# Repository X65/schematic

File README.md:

# X65

Modern 8-bit microcomputer

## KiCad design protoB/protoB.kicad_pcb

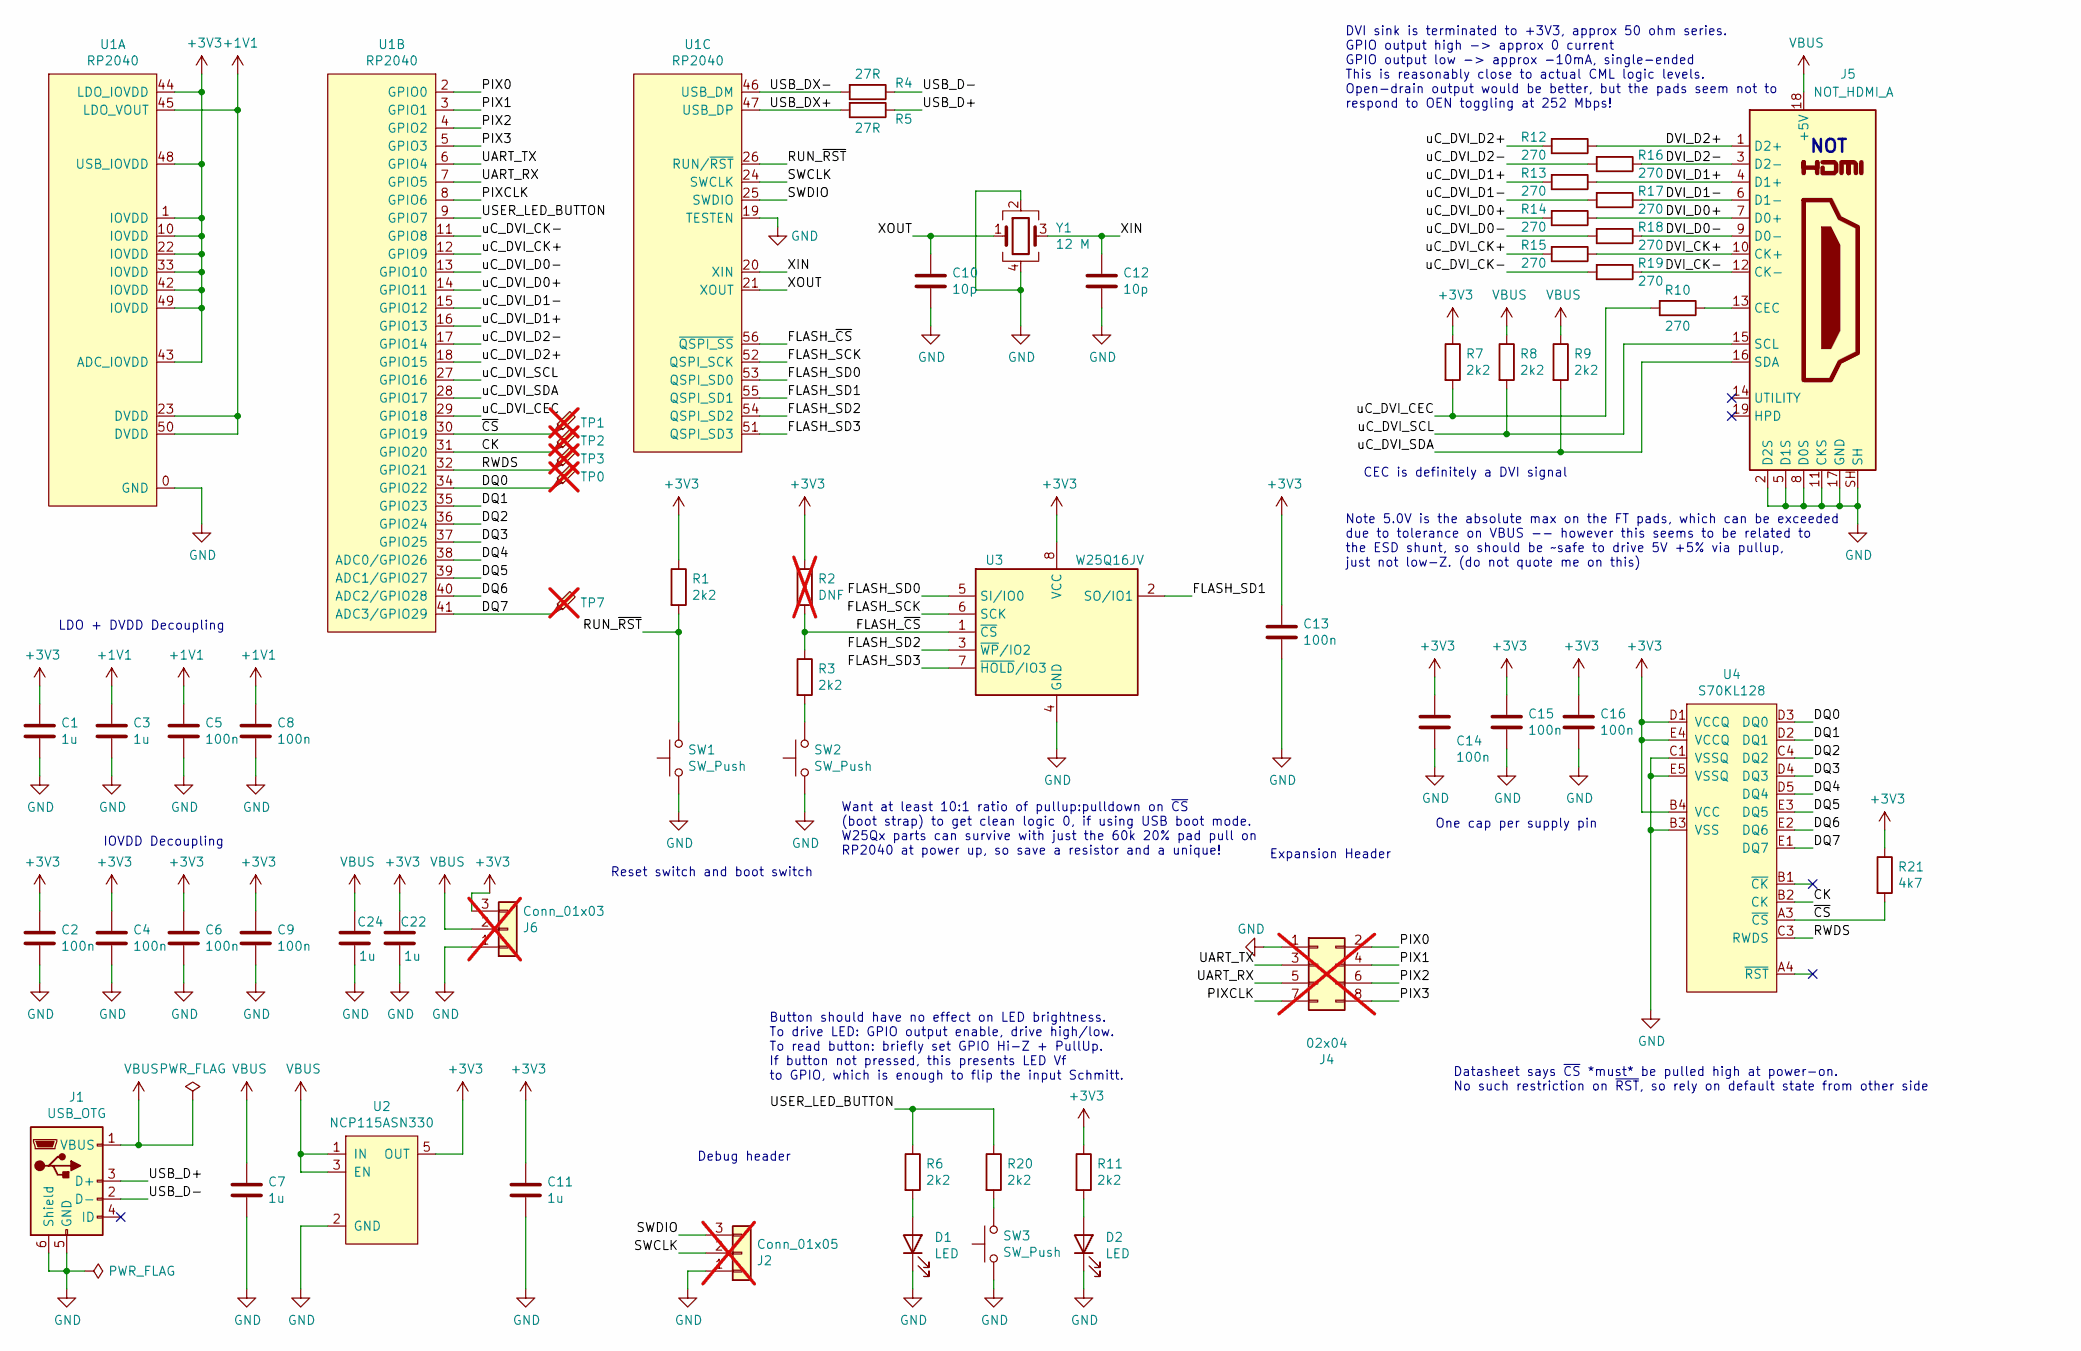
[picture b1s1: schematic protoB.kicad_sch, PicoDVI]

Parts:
C1, C3, C7, C11, C22, C24: 1u; C_0402_1005Metric; Manuf. PN CL05A105KP5NNNC
C2, C4, C5, C6, C8, C9, C13, C14, C15, C16: 100n; C_0402_1005Metric; Manuf. PN CL05A104KP5NNND
C10, C12: 10p; C_0402_1005Metric; Manuf. PN CL05C100JB5NNWC
D1, D2: LED; LED_0805_2012Metric; Manuf. PN LG R971-KN-1
J1: USB_OTG; USB_Micro-B_Molex-105017-0001; Manuf. PN 10118194-0001LF
J2: Conn_01x05; PinHeader_1x03_P2.54mm_Vertical; not fitted
J4: 02x04; PinHeader_2x04_P2.54mm_Vertical; not fitted
J5: NOT_HDMI_A; HDMI-SS-53000; Manuf. PN SS-53000-001
J6: Conn_01x03; PinHeader_1x03_P2.54mm_Vertical; not fitted
R1, R3, R6, R7, R8, R9, R11, R20: 2k2; R_0402_1005Metric; Manuf. PN ERJ-2GEJ222X
R2: DNF; R_0402_1005Metric; not fitted
R4, R5: 27R; R_0402_1005Metric; Manuf. PN ERJ-2GEJ270X
R10, R12, R13, R14, R15, R16, R17, R18, R19: 270; R_0402_1005Metric; Manuf. PN ERJ-2GEJ271X
R21: 4k7; R_0402_1005Metric; Manuf. PN ERJ-2GEJ472X
SW1, SW2, SW3: SW_Push; SW_SPST_PTS815; Manuf. PN TS20-42-25-WT-160-SMT-TR
TP0, TP1, TP2, TP3, TP7: TestPoint_Probe; TestPoint_Pad_1.0x1.0mm; not fitted
U1: RP2040; QFN-56_EP_7x7_Pitch0.4mm; Manuf. PN SC0914(13)
U2: NCP115ASN330; SOT-23-5_HandSoldering; Manuf. PN NCP115ASN330T2G
U3: W25Q16JV; WSON-8-1EP_6x5mm_P1.27mm_EP3.4x4mm; Manuf. PN W25Q16JVZPIM
U4: S70KL128; S70KS128; Manuf. PN S70KL1282GABHV020
Y1: 12 M; Crystal_SMD_3225-4Pin_3.2x2.5mm; Manuf. PN ABM8G-12.000MHZ-8-B2X-T

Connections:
+1V1: C3.1, C5.1, C8.1, U1.23 (DVDD), U1.45 (LDO_VOUT), U1.50 (DVDD)
+3V3: C1.1, C2.1, C4.1, C6.1, C9.1, C11.1, C13.1, C14.1, C15.1, C16.1, C22.1, J6.3, R1.1, R2.1, R7.1, R11.1, R21.1, U1.1 (IOVDD), U1.10 (IOVDD), U1.22 (IOVDD), U1.33 (IOVDD), U1.42 (IOVDD), U1.43 (ADC_IOVDD), U1.44 (LDO_IOVDD), U1.48 (USB_IOVDD), U1.49 (IOVDD), U2.5 (OUT), U3.8 (VCC), U4.B4 (VCC), U4.D1 (VCCQ), U4.E4 (VCCQ)
/CK: TP2.1, U1.31 (GPIO20), U4.B2 (CK)
/DQ0: TP0.1, U1.34 (GPIO22), U4.D3 (DQ0)
/DQ1: U1.35 (GPIO23), U4.D2 (DQ1)
/DQ2: U1.36 (GPIO24), U4.C4 (DQ2)
/DQ3: U1.37 (GPIO25), U4.D4 (DQ3)
/DQ4: U1.38 (ADC0/GPIO26), U4.D5 (DQ4)
/DQ5: U1.39 (ADC1/GPIO27), U4.E3 (DQ5)
/DQ6: U1.40 (ADC2/GPIO28), U4.E2 (DQ6)
/DQ7: TP7.1, U1.41 (ADC3/GPIO29), U4.E1 (DQ7)
/DVI_CK+: J5.10 (CK+), R15.1
/DVI_CK-: J5.12 (CK-), R19.1
/DVI_D0+: J5.7 (D0+), R14.1
/DVI_D0-: J5.9 (D0-), R18.1
/DVI_D1+: J5.4 (D1+), R13.1
/DVI_D1-: J5.6 (D1-), R17.1
/DVI_D2+: J5.1 (D2+), R12.1
/DVI_D2-: J5.3 (D2-), R16.1
/FLASH_SCK: U1.52 (QSPI_SCK), U3.6 (SCK)
/FLASH_SD0: U1.53 (QSPI_SD0), U3.5 (SI/IO0)
/FLASH_SD1: U1.55 (QSPI_SD1), U3.2 (SO/IO1)
/FLASH_SD2: U1.54 (QSPI_SD2), U3.3 (~WP/IO2)
/FLASH_SD3: U1.51 (QSPI_SD3), U3.7 (~HOLD/IO3)
/FLASH_~CS: R2.2, R3.1, U1.56 (~QSPI_SS), U3.1 (~CS)
/PIX0: J4.2, U1.2 (GPIO0)
/PIX1: J4.4, U1.3 (GPIO1)
/PIX2: J4.6, U1.4 (GPIO2)
/PIX3: J4.8, U1.5 (GPIO3)
/PIXCLK: J4.7, U1.8 (GPIO6)
/RUN_~RST: R1.2, SW1.2, U1.26 (RUN/~RST)
/RWDS: TP3.1, U1.32 (GPIO21), U4.C3 (RWDS)
/SWCLK: J2.2, U1.24 (SWCLK)
/SWDIO: J2.3, U1.25 (SWDIO)
/UART_RX: J4.5, U1.7 (GPIO5)
/UART_TX: J4.3, U1.6 (GPIO4)
/USB_D+: J1.3 (D+), R5.1
/USB_D-: J1.2 (D-), R4.1
/USB_DX+: R5.2, U1.47 (USB_DP)
/USB_DX-: R4.2, U1.46 (USB_DM)
/USER_LED_BUTTON: R6.1, R20.1, U1.9 (GPIO7)
/XIN: C12.1, U1.20 (XIN), Y1.3
/XOUT: C10.1, U1.21 (XOUT), Y1.1
/uC_DVI_CEC: R7.2, R10.2, U1.29 (GPIO18)
/uC_DVI_CK+: R15.2, U1.12 (GPIO9)
/uC_DVI_CK-: R19.2, U1.11 (GPIO8)
/uC_DVI_D0+: R14.2, U1.14 (GPIO11)
/uC_DVI_D0-: R18.2, U1.13 (GPIO10)
/uC_DVI_D1+: R13.2, U1.16 (GPIO13)
/uC_DVI_D1-: R17.2, U1.15 (GPIO12)
/uC_DVI_D2+: R12.2, U1.18 (GPIO15)
/uC_DVI_D2-: R16.2, U1.17 (GPIO14)
/uC_DVI_SCL: J5.15 (SCL), R8.2, U1.27 (GPIO16)
/uC_DVI_SDA: J5.16 (SDA), R9.2, U1.28 (GPIO17)
/~CS: R21.2, TP1.1, U1.30 (GPIO19), U4.A3 (~CS)
GND: C1.2, C2.2, C3.2, C4.2, C5.2, C6.2, C7.2, C8.2, C9.2, C10.2, C11.2, C12.2, C13.2, C14.2, C15.2, C16.2, C22.2, C24.2, D1.1 (K), D2.1 (K), J1.5 (GND), J1.6 (Shield), J2.1, J4.1, J5.2 (D2S), J5.5 (D1S), J5.8 (D0S), J5.11 (CKS), J5.17 (GND), J5.SH, J6.1, SW1.1, SW2.1, SW3.1, U1.0 (GND), U1.19 (TESTEN), U2.2 (GND), U3.4 (GND), U4.B3 (VSS), U4.C1 (VSSQ), U4.E5 (VSSQ), Y1.2, Y1.4
unnamed: D1.2 (A), R6.2
unnamed: D2.2 (A), R11.2
unnamed: J5.13 (CEC), R10.1
unnamed: R3.2, SW2.2
unnamed: R20.2, SW3.2
VBUS: C7.1, C24.1, J1.1 (VBUS), J5.18 (+5V), J6.2, R8.1, R9.1, U2.1 (IN), U2.3 (EN)

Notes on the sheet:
Reset switch and boot switch
DVI sink is terminated to +3V3, approx 50 ohm series. GPIO output high -> approx 0 current GPIO output low -> approx -10mA, single-ended This is reasonably close to actual CML logic levels. Open-drain output would be better, but the pads seem not to respond to OEN toggling at 252 Mbps!
Note 5.0V is the absolute max on the FT pads, which can be exceeded due to tolerance on VBUS -- however this seems to be related to the ESD shunt, so should be ~safe to drive 5V +5% via pullup, just not low-Z. (do not quote me on this)
Expansion Header
CEC is definitely a DVI signal
Debug header
One cap per supply pin
Button should have no effect on LED brightness. To drive LED: GPIO output enable, drive high/low. To read button: briefly set GPIO Hi-Z + PullUp. If button not pressed, this presents LED Vf to GPIO, which is enough to flip the input Schmitt.
NOT
IOVDD Decoupling
Want at least 10:1 ratio of pullup:pulldown on ~{CS} (boot strap) to get clean logic 0, if using USB boot mode. W25Qx parts can survive with just the 60k 20% pad pull on RP2040 at power up, so save a resistor and a unique!
LDO + DVDD Decoupling
Datasheet says ~{CS} *must* be pulled high at power-on. No such restriction on ~{RST}, so rely on default state from other side

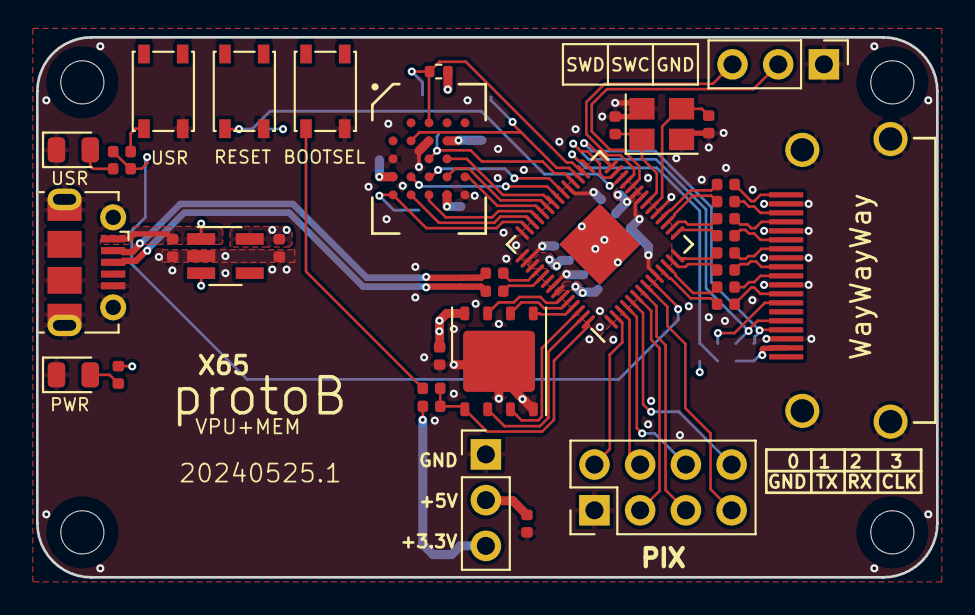
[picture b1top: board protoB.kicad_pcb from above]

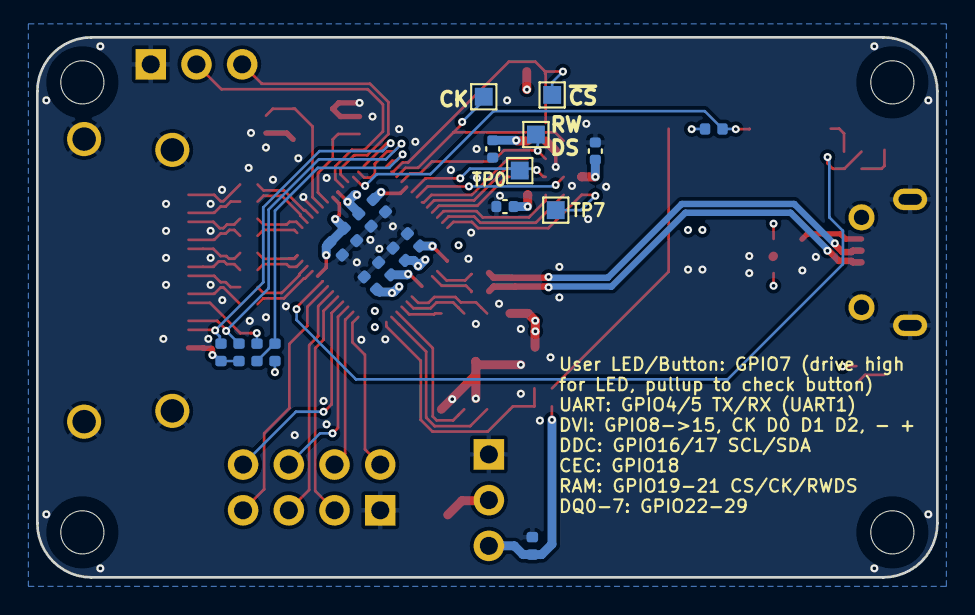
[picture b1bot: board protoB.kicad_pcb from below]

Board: 4 copper layers, 50.0 x 30.0 mm, 59 parts (22 on the bottom side), 62 nets.

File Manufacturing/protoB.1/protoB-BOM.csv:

"Reference","Value","Footprint","Qty","Description","Manufacturer","Manufacturer Part Number","Distributor Link"
"C1,C3,C7,C11,C22,C24","1u","Capacitor_SMD:C_0402_1005Metric","6","","Samsung Electro-Mechanics","CL05A105KP5NNNC","https://mou.sr/4bECjGk"
"C2,C4,C5,C6,C8,C9,C13,C14,C15,C16","100n","Capacitor_SMD:C_0402_1005Metric","10","","Samsung Electro-Mechanics","CL05A104KP5NNND","https://mou.sr/3KdZBGS"
"C10,C12","10p","Capacitor_SMD:C_0402_1005Metric","2","","Samsung Electro-Mechanics","CL05C100JB5NNWC","https://mou.sr/3wG0dC5"
"D1,D2","LED","LED_SMD:LED_0805_2012Metric","2","","ams OSRAM","LG R971-KN-1","https://mou.sr/4bR62v3"
"J1","USB_OTG","Connector_USB:USB_Micro-B_Molex-105017-0001","1","","Amphenol FCI","10118194-0001LF","https://mou.sr/4dT1d6p"
"J5","NOT_HDMI_A","picodvi:HDMI-SS-53000","1","","Stewart Connector / Bel","SS-53000-001","https://mou.sr/3yy3Z0K"
"R1,R3,R6,R7,R8,R9,R11,R20","2k2","Resistor_SMD:R_0402_1005Metric","8","","Panasonic","ERJ-2GEJ222X","https://mou.sr/3Ko4NYx"
"R4,R5","27R","Resistor_SMD:R_0402_1005Metric","2","","Panasonic","ERJ-2GEJ270X","https://mou.sr/4aDuT4K"
"R10,R12,R13,R14,R15,R16,R17,R18,R19","270","Resistor_SMD:R_0402_1005Metric","9","","Panasonic","ERJ-2GEJ271X","https://mou.sr/3R2dc7N"
"R21","4k7","Resistor_SMD:R_0402_1005Metric","1","","Panasonic","ERJ-2GEJ472X","https://mou.sr/3WW8RXu"
"SW1,SW2,SW3","SW_Push","picodvi:SW_SPST_PTS815","3","","CUI Devices","TS20-42-25-WT-160-SMT-TR","https://mou.sr/3QW06J9"
"U1","RP2040","picodvi:QFN-56_EP_7x7_Pitch0.4mm","1","","Raspberry Pi","SC0914(13)","https://mou.sr/3yzMLAh"
"U2","NCP115ASN330","Package_TO_SOT_SMD:SOT-23-5_HandSoldering","1","","onsemi","NCP115ASN330T2G","https://mou.sr/3XPpim0"
"U3","W25Q16JV","Package_SON:WSON-8-1EP_6x5mm_P1.27mm_EP3.4x4mm","1","","Winbond","W25Q16JVZPIM","https://mou.sr/3QZBQWG"
"U4","S70KL128","picodvi:S70KS128","1","","Infineon Technologies","S70KL1282GABHV020","https://mou.sr/4aGu1MC"
"Y1","12 M","Crystal:Crystal_SMD_3225-4Pin_3.2x2.5mm","1","","ABRACON","ABM8G-12.000MHZ-8-B2X-T","https://mou.sr/4aD4eFh"

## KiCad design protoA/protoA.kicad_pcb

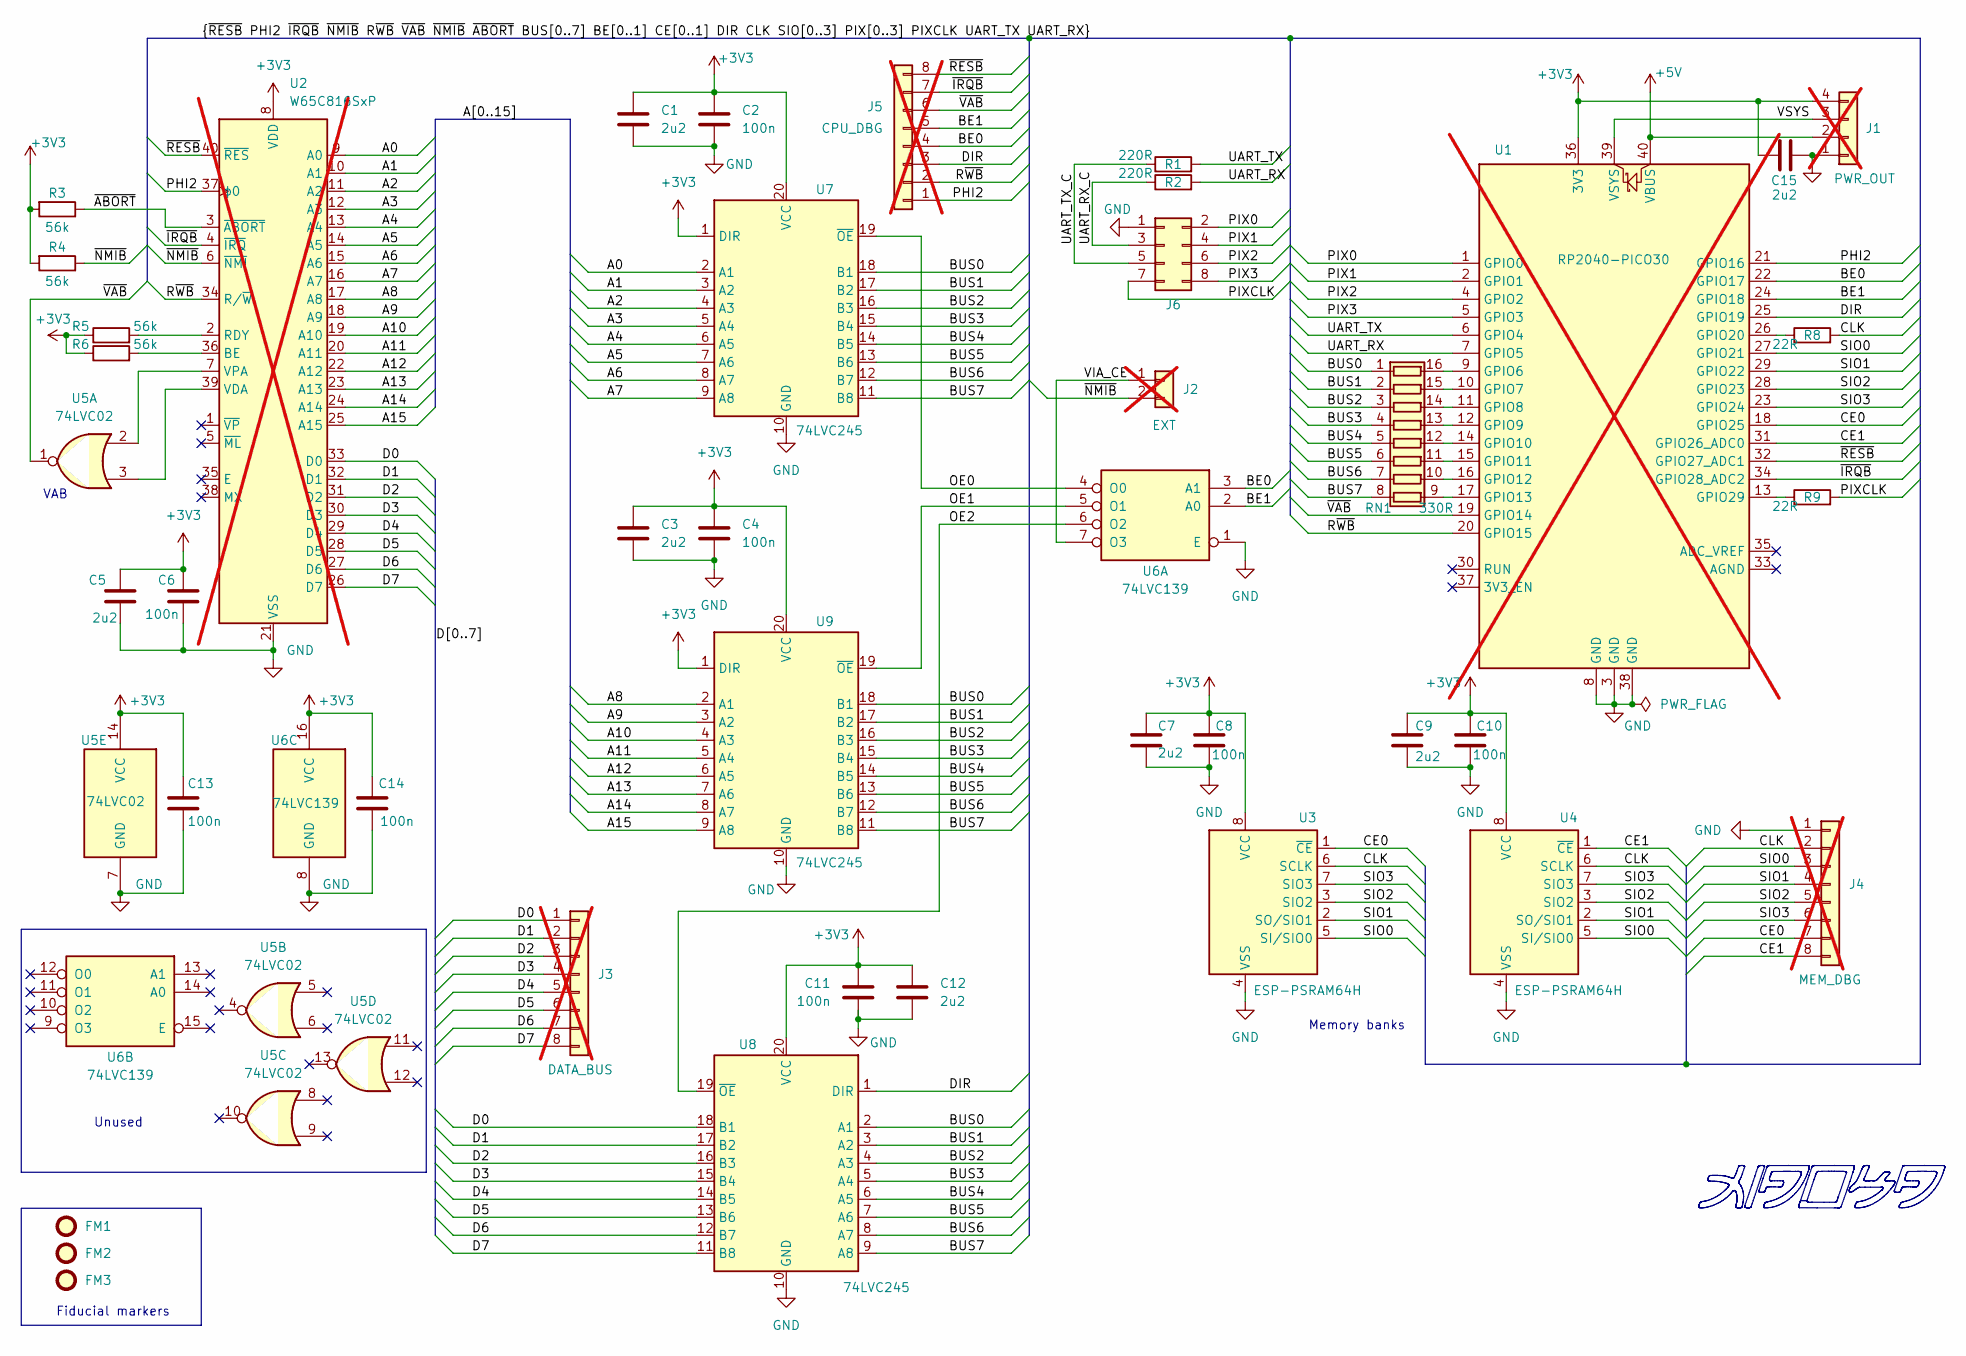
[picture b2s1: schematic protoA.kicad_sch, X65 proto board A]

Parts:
C1, C3, C5, C7, C9, C12, C15: 2u2; C_0603_1608Metric; Manufacturer Part Number CL10A225KP8NNNC
C2, C4, C6, C8, C10, C11, C13, C14: 100n; C_0402_1005Metric; Manufacturer Part Number CL05B104KO5VPNC
FM1, FM2, FM3: Fiducial; Fiducial_1mm_Mask2mm
J1: PWR_OUT; PinHeader_1x04_P1.00mm_Vertical; not fitted
J2: EXT; PinHeader_1x02_P1.00mm_Vertical; not fitted
J3: DATA_BUS; PinHeader_1x08_P1.00mm_Vertical; not fitted
J4: MEM_DBG; PinHeader_1x08_P1.00mm_Vertical; not fitted
J5: CPU_DBG; PinHeader_1x08_P1.00mm_Vertical; not fitted
J6: PIX; IDC-Header_2x04_P2.54mm_Vertical; Manufacturer Part Number 70246-0801
R1, R2: 220R; R_0402_1005Metric; Manufacturer Part Number ERJ-2GEJ221X
R3, R4, R5, R6: 56k; R_0402_1005Metric; Manufacturer Part Number ERJ-2GEJ563X
R8, R9: 22R; R_0402_1005Metric; Manufacturer Part Number ERJ-2RKF22R0X
RN1: 330R; R_Array_Convex_8x0602; Manufacturer Part Number EXB-2HV331JV
U1: RP2040-PICO30; RaspberryPi_Pico_Common; not fitted
U2: W65C816SxP; DIP-40_W15.24mm_Socket; Manufacturer Part Number W65C816S6PG-14; not fitted
U3, U4: ESP-PSRAM64H; SOIC-8_3.9x4.9mm_P1.27mm; Manufacturer Part Number 4677
U5: 74LVC02; TSSOP-14_4.4x5mm_P0.65mm; Manufacturer Part Number SN74LVC02APWR
U6: 74LVC139; TSSOP-16_4.4x5mm_P0.65mm; Manufacturer Part Number SN74LVC139APWR
U7, U8, U9: 74LVC245; TSSOP-20_4.4x6.5mm_P0.65mm; Manufacturer Part Number SN74LVC245APWR

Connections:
+3V3: C1.1, C2.1, C3.1, C4.1, C5.2, C6.1, C7.1, C8.1, C9.1, C10.1, C11.1, C12.1, C13.1, C14.1, C15.1, J1.4, R3.2, R4.2, R5.1, R6.1, U1.36 (3V3), U2.8 (VDD), U3.8 (VCC), U4.8 (VCC), U5.14 (VCC), U6.16 (VCC), U7.1 (DIR), U7.20 (VCC), U8.20 (VCC), U9.1 (DIR), U9.20 (VCC)
+5V: J1.2, U1.40 (VBUS)
/A0: U2.9 (A0), U7.2 (A1)
/A1: U2.10 (A1), U7.3 (A2)
/A2: U2.11 (A2), U7.4 (A3)
/A3: U2.12 (A3), U7.5 (A4)
/A4: U2.13 (A4), U7.6 (A5)
/A5: U2.14 (A5), U7.7 (A6)
/A6: U2.15 (A6), U7.8 (A7)
/A7: U2.16 (A7), U7.9 (A8)
/A8: U2.17 (A8), U9.2 (A1)
/A9: U2.18 (A9), U9.3 (A2)
/A10: U2.19 (A10), U9.4 (A3)
/A11: U2.20 (A11), U9.5 (A4)
/A12: U2.22 (A12), U9.6 (A5)
/A13: U2.23 (A13), U9.7 (A6)
/A14: U2.24 (A14), U9.8 (A7)
/A15: U2.25 (A15), U9.9 (A8)
/BE0: J5.4, U1.22 (GPIO17), U6.3 (A1)
/BE1: J5.5, U1.24 (GPIO18), U6.2 (A0)
/BUS0: RN1.1 (R1.1), U7.18 (B1), U8.2 (A1), U9.18 (B1)
/BUS1: RN1.2 (R2.1), U7.17 (B2), U8.3 (A2), U9.17 (B2)
/BUS2: RN1.3 (R3.1), U7.16 (B3), U8.4 (A3), U9.16 (B3)
/BUS3: RN1.4 (R4.1), U7.15 (B4), U8.5 (A4), U9.15 (B4)
/BUS4: RN1.5 (R5.1), U7.14 (B5), U8.6 (A5), U9.14 (B5)
/BUS5: RN1.6 (R6.1), U7.13 (B6), U8.7 (A6), U9.13 (B6)
/BUS6: RN1.7 (R7.1), U7.12 (B7), U8.8 (A7), U9.12 (B7)
/BUS7: RN1.8 (R8.1), U7.11 (B8), U8.9 (A8), U9.11 (B8)
/CE0: J4.7, U1.18 (GPIO25), U3.1 (~CE)
/CE1: J4.8, U1.31 (GPIO26_ADC0), U4.1 (~CE)
/CLK: J4.2, R8.2, U3.6 (SCLK), U4.6 (SCLK)
/D0: J3.1, U2.33 (D0), U8.18 (B1)
/D1: J3.2, U2.32 (D1), U8.17 (B2)
/D2: J3.3, U2.31 (D2), U8.16 (B3)
/D3: J3.4, U2.30 (D3), U8.15 (B4)
/D4: J3.5, U2.29 (D4), U8.14 (B5)
/D5: J3.6, U2.28 (D5), U8.13 (B6)
/D6: J3.7, U2.27 (D6), U8.12 (B7)
/D7: J3.8, U2.26 (D7), U8.11 (B8)
/DIR: J5.3, U1.25 (GPIO19), U8.1 (DIR)
/OE0: U6.4 (O0), U7.19 (~OE)
/OE1: U6.5 (O1), U9.19 (~OE)
/OE2: U6.6 (O2), U8.19 (~OE)
/PHI2: J5.1, U1.21 (GPIO16), U2.37 (ϕ0)
/PIX0: J6.2, U1.1 (GPIO0)
/PIX1: J6.4, U1.2 (GPIO1)
/PIX2: J6.6, U1.4 (GPIO2)
/PIX3: J6.8, U1.5 (GPIO3)
/PIXCLK: J6.7, R9.2
/R~WB: J5.2, U1.20 (GPIO15), U2.34 (R/~W)
/SIO0: J4.3, U1.27 (GPIO21), U3.5 (SI/SIO0), U4.5 (SI/SIO0)
/SIO1: J4.4, U1.29 (GPIO22), U3.2 (SO/SIO1), U4.2 (SO/SIO1)
/SIO2: J4.5, U1.28 (GPIO23), U3.3 (SIO2), U4.3 (SIO2)
/SIO3: J4.6, U1.23 (GPIO24), U3.7 (SIO3), U4.7 (SIO3)
/UART_RX: R2.2, U1.7 (GPIO5)
/UART_RX_C: J6.3, R2.1
/UART_TX: R1.2, U1.6 (GPIO4)
/UART_TX_C: J6.5, R1.1
/VIA_CE: J2.1, U6.7 (O3)
/VSYS: J1.3, U1.39 (VSYS)
/~ABORT: R3.1, U2.3 (~ABORT)
/~IRQB: J5.7, U1.34 (GPIO28_ADC2), U2.4 (~IRQ)
/~NMIB: J2.2, R4.1, U2.6 (~NMI)
/~RESB: J5.8, U1.32 (GPIO27_ADC1), U2.40 (~RES)
/~VAB: J5.6, U1.19 (GPIO14), U5.1
GND: C1.2, C2.2, C3.2, C4.2, C5.1, C6.2, C7.2, C8.2, C9.2, C10.2, C11.2, C12.2, C13.2, C14.2, C15.2, J1.1, J4.1, J6.1, U1.3 (GND), U1.8 (GND), U1.38 (GND), U2.21 (VSS), U3.4 (VSS), U4.4 (VSS), U5.7 (GND), U6.1 (E), U6.8 (GND), U7.10 (GND), U8.10 (GND), U9.10 (GND)
unnamed: RN1.16 (R1.2), U1.9 (GPIO6)
unnamed: RN1.15 (R2.2), U1.10 (GPIO7)
unnamed: RN1.14 (R3.2), U1.11 (GPIO8)
unnamed: RN1.13 (R4.2), U1.12 (GPIO9)
unnamed: RN1.12 (R5.2), U1.14 (GPIO10)
unnamed: RN1.11 (R6.2), U1.15 (GPIO11)
unnamed: RN1.10 (R7.2), U1.16 (GPIO12)
unnamed: RN1.9 (R8.2), U1.17 (GPIO13)
unnamed: R8.1, U1.26 (GPIO20)
unnamed: R9.1, U1.13 (GPIO29)
unnamed: R6.2, U2.36 (BE)
unnamed: R5.2, U2.2 (RDY)
unnamed: U2.39 (VDA), U5.3
unnamed: U2.7 (VPA), U5.2

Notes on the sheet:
Fiducial markers
Unused
VAB
Memory banks

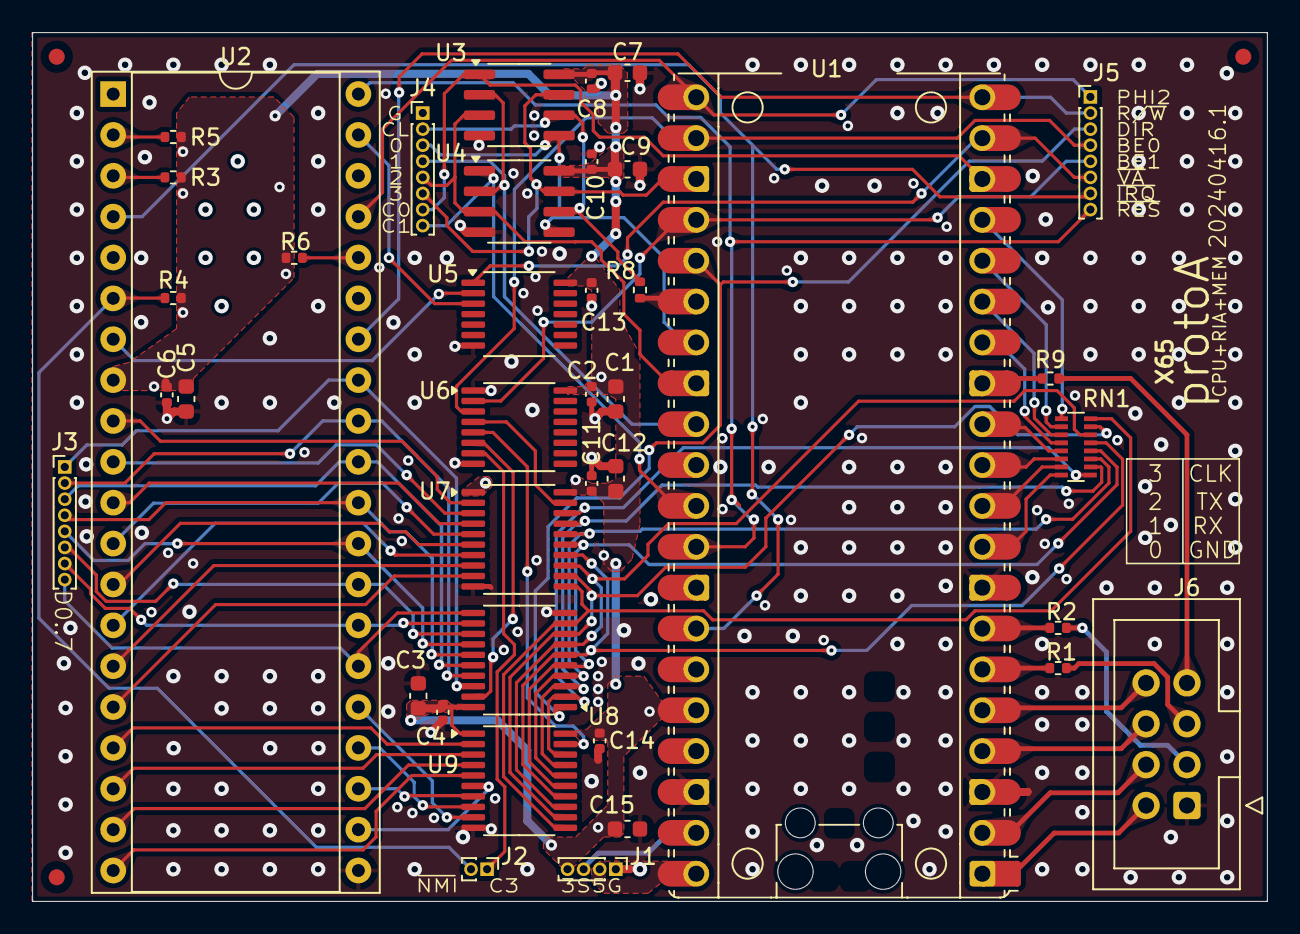
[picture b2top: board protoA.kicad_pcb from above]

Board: 4 copper layers, 76.8 x 54.0 mm, 42 parts (0 on the bottom side), 80 nets.

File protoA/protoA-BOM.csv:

"Reference","Value","Footprint","Qty","Description","Manufacturer","Manufacturer Part Number","Distributor Link"
"C1,C3,C5,C7,C9,C12,C15","2u2","Capacitor_SMD:C_0603_1608Metric","7","Unpolarized capacitor","Samsung","CL10A225KP8NNNC","https://mou.sr/3w2rYEg"
"C2,C4,C6,C8,C10,C11,C13,C14","100n","Capacitor_SMD:C_0402_1005Metric","8","Unpolarized capacitor","Samsung","CL05B104KO5VPNC","https://mou.sr/3xGMjjb"
"J6","PIX","Connector_IDC:IDC-Header_2x04_P2.54mm_Vertical","1","IDC connector, double row, 02x04, odd/even pin numbering scheme (row 1 odd numbers, row 2 even numbers)","Amphenol FCI","71600-108LF","https://mou.sr/3Jhh3d6"
"R1,R2","220R","Resistor_SMD:R_0402_1005Metric","2","Resistor","Panasonic"," ERJ-2GEJ221X","https://mou.sr/4aBofNf"
"R3,R4,R5,R6","56k","Resistor_SMD:R_0402_1005Metric","4","Resistor","Panasonic","ERJ-2GEJ563X","https://mou.sr/49zQz12"
"R8,R9","22R","Resistor_SMD:R_0402_1005Metric","2","Resistor","Panasonic","ERJ-2RKF22R0X","https://mou.sr/4b0pJA7"
"RN1","330R","Resistor_SMD:R_Array_Convex_8x0602","1","8 resistor network, parallel topology","Panasonic","EXB-2HV331JV","https://mou.sr/3vZmbiL"
"U3,U4","ESP-PSRAM64H","Package_SO:SOIC-8_3.9x4.9mm_P1.27mm","2","64 Mbit serial pseudo SRAM device organized as 8Mx8 bits, 3.3 VCC, SOIC8 (SOP8)","Adafruit ","4677","https://mou.sr/3vCkKqE"
"U5","74LVC02","Package_SO:TSSOP-14_4.4x5mm_P0.65mm","1","quad 2-input NOR gate","TI","SN74LVC02APWR","https://mou.sr/3Udvfdg"
"U6","74LVC139","Package_SO:TSSOP-16_4.4x5mm_P0.65mm","1","Dual Decoder 1 of 4, Active low outputs","TI","SN74LVC139APWR ","https://mou.sr/3UeJ8aY"
"U7,U8,U9","74LVC245","Package_SO:TSSOP-20_4.4x6.5mm_P0.65mm","3","8-Bit Single-Supply Bus Transceiver With 3-State Outputs, TSSOP-20","TI","SN74LVC245APWR","https://mou.sr/4alyB3z"

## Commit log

2024-03-13 Import https://gitlab.com/recursivenomad/ki-lime-pi-pico
2024-03-13 Schematics of protoA board
2024-04-11 protoA ERC Pass
2024-04-11 protoA footprints and BOM
2024-04-16 protoA PCB done
2024-04-17 protoA BOM update
2024-04-17 protoA Manufacturing files
2024-04-17 protoA Fabrication drawing
2024-05-02 Fix J6 PIX connector BOM designator
2024-05-26 Rename protoA to protoA.1
2024-05-26 Add protoB schematic, board and manufacturing
2024-05-31 Remove and ignore backups
2024-07-16 Add protoB.pdf schematic
2024-10-21 protoC PDF
2025-05-15 Simplified Interrupt Controller
2025-05-18 Update protoC
2025-06-23 Production rev1
2025-06-26 Add protoC STEP export
